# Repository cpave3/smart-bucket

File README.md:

# smart-bucket
Things relating to the smart bucket K40 cooling project

## TODO:

- [x] ESP Home Firmware
- [ ] KiCAD designs
- [ ] FreeCAD designs
- [ ] Wireviz designs

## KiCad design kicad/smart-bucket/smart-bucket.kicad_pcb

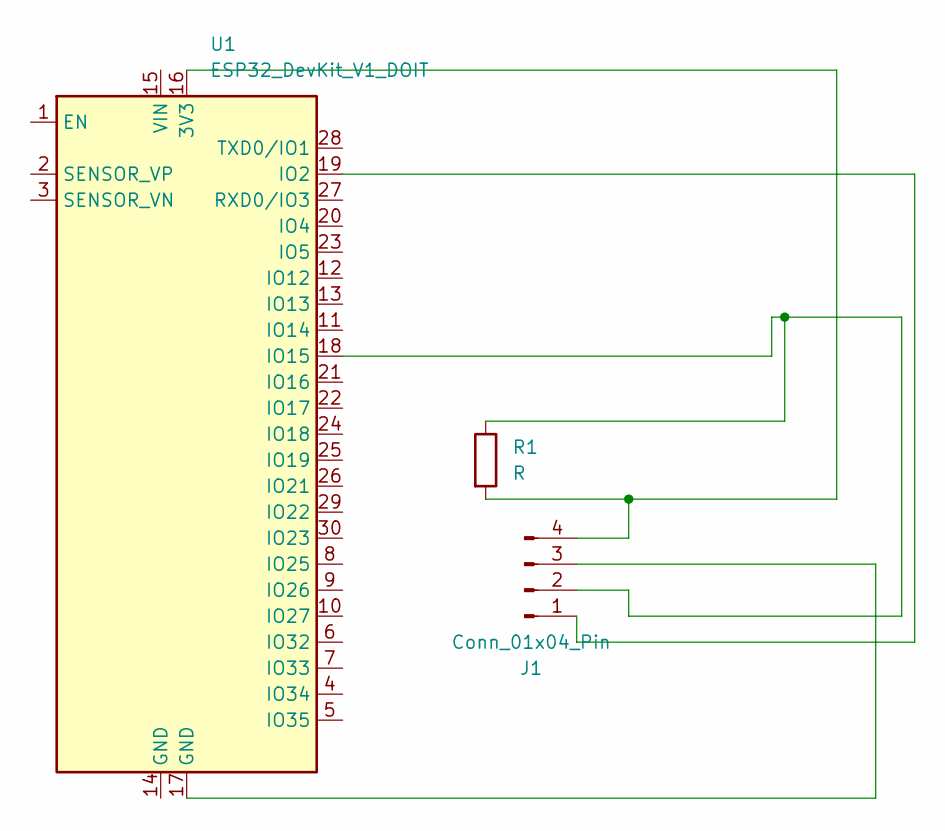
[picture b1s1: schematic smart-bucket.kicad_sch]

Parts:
J1: Conn_01x04_Pin; JST_XH_B4B-XH-AM_1x04_P2.50mm_Vertical
R1: R; R_Axial_DIN0207_L6.3mm_D2.5mm_P5.08mm_Vertical
U1: ESP32_DevKit_V1_DOIT; esp32_devkit_v1_doit

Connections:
unnamed: J1.1, U1.19 (IO2)
unnamed: J1.2, R1.1, U1.18 (IO15)
unnamed: J1.3, U1.17 (GND)
unnamed: J1.4, R1.2, U1.16 (3V3)

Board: 2 copper layers, 3 parts (0 on the bottom side), 4 nets, no tracks yet.

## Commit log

2024-04-27 chore: update readme
2024-04-28 chore: add basic design
2024-05-06 wip: add esphome firmware to repo
